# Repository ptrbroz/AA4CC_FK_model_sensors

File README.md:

# AA4CC_FK_model_sensors

FK_quadrature_decoder - DE0-Nano firmware for quadrature decoding and communication. Also includes folders from PC-side communication (python and matlab)

FK_fpga_shield - shield to be placed upon DE0-Nano

FK_encoder_shield - shield to be connected to each incremental encoder

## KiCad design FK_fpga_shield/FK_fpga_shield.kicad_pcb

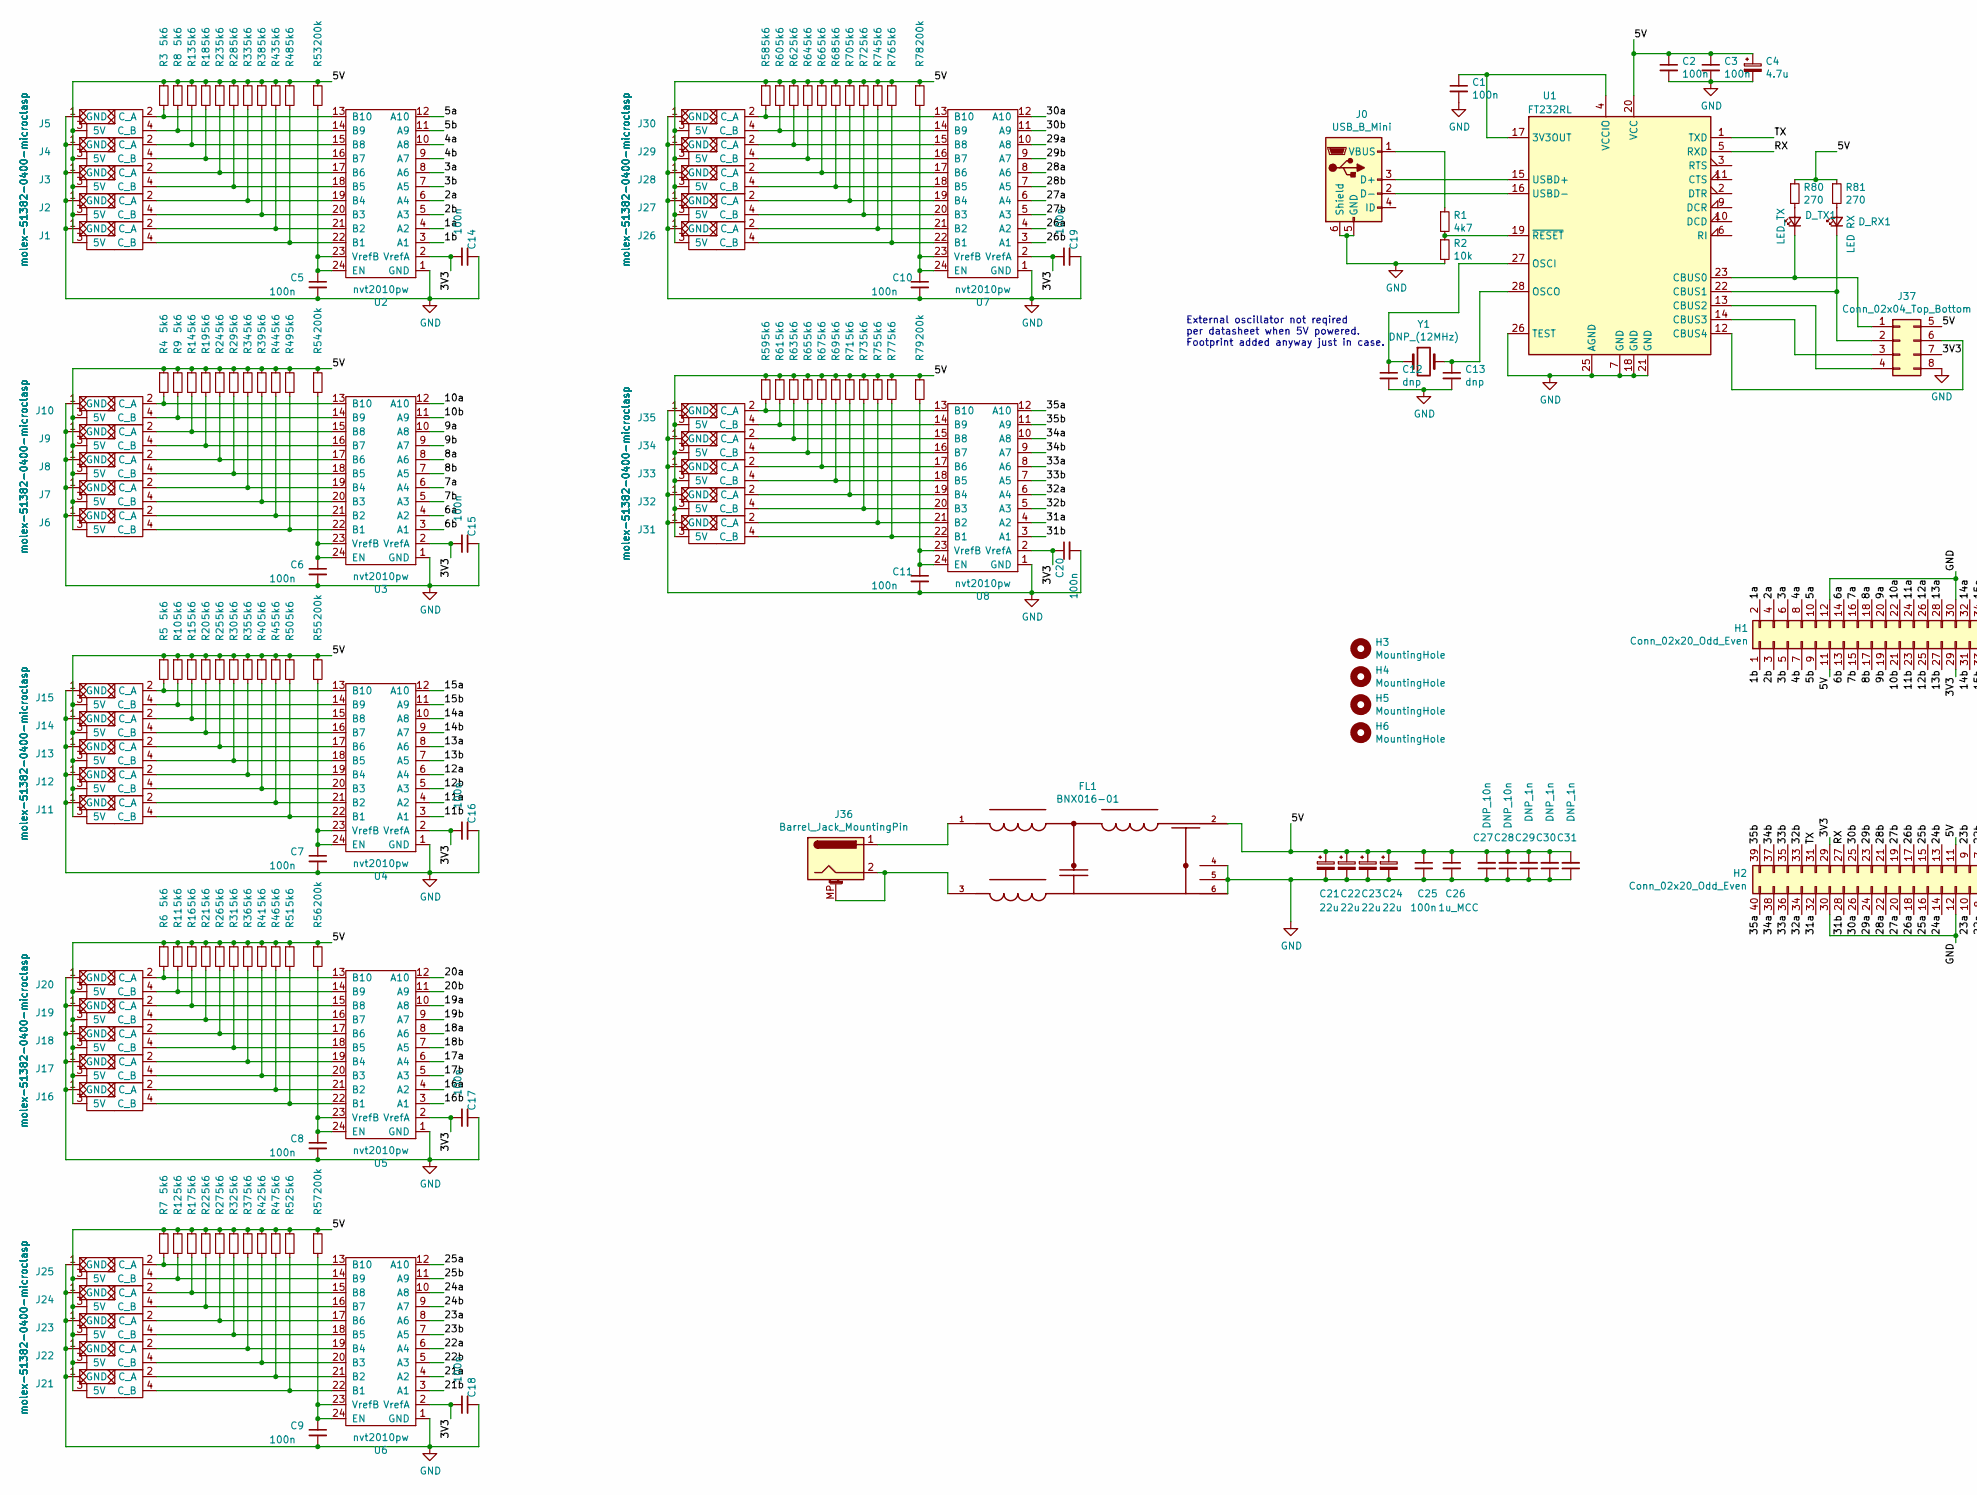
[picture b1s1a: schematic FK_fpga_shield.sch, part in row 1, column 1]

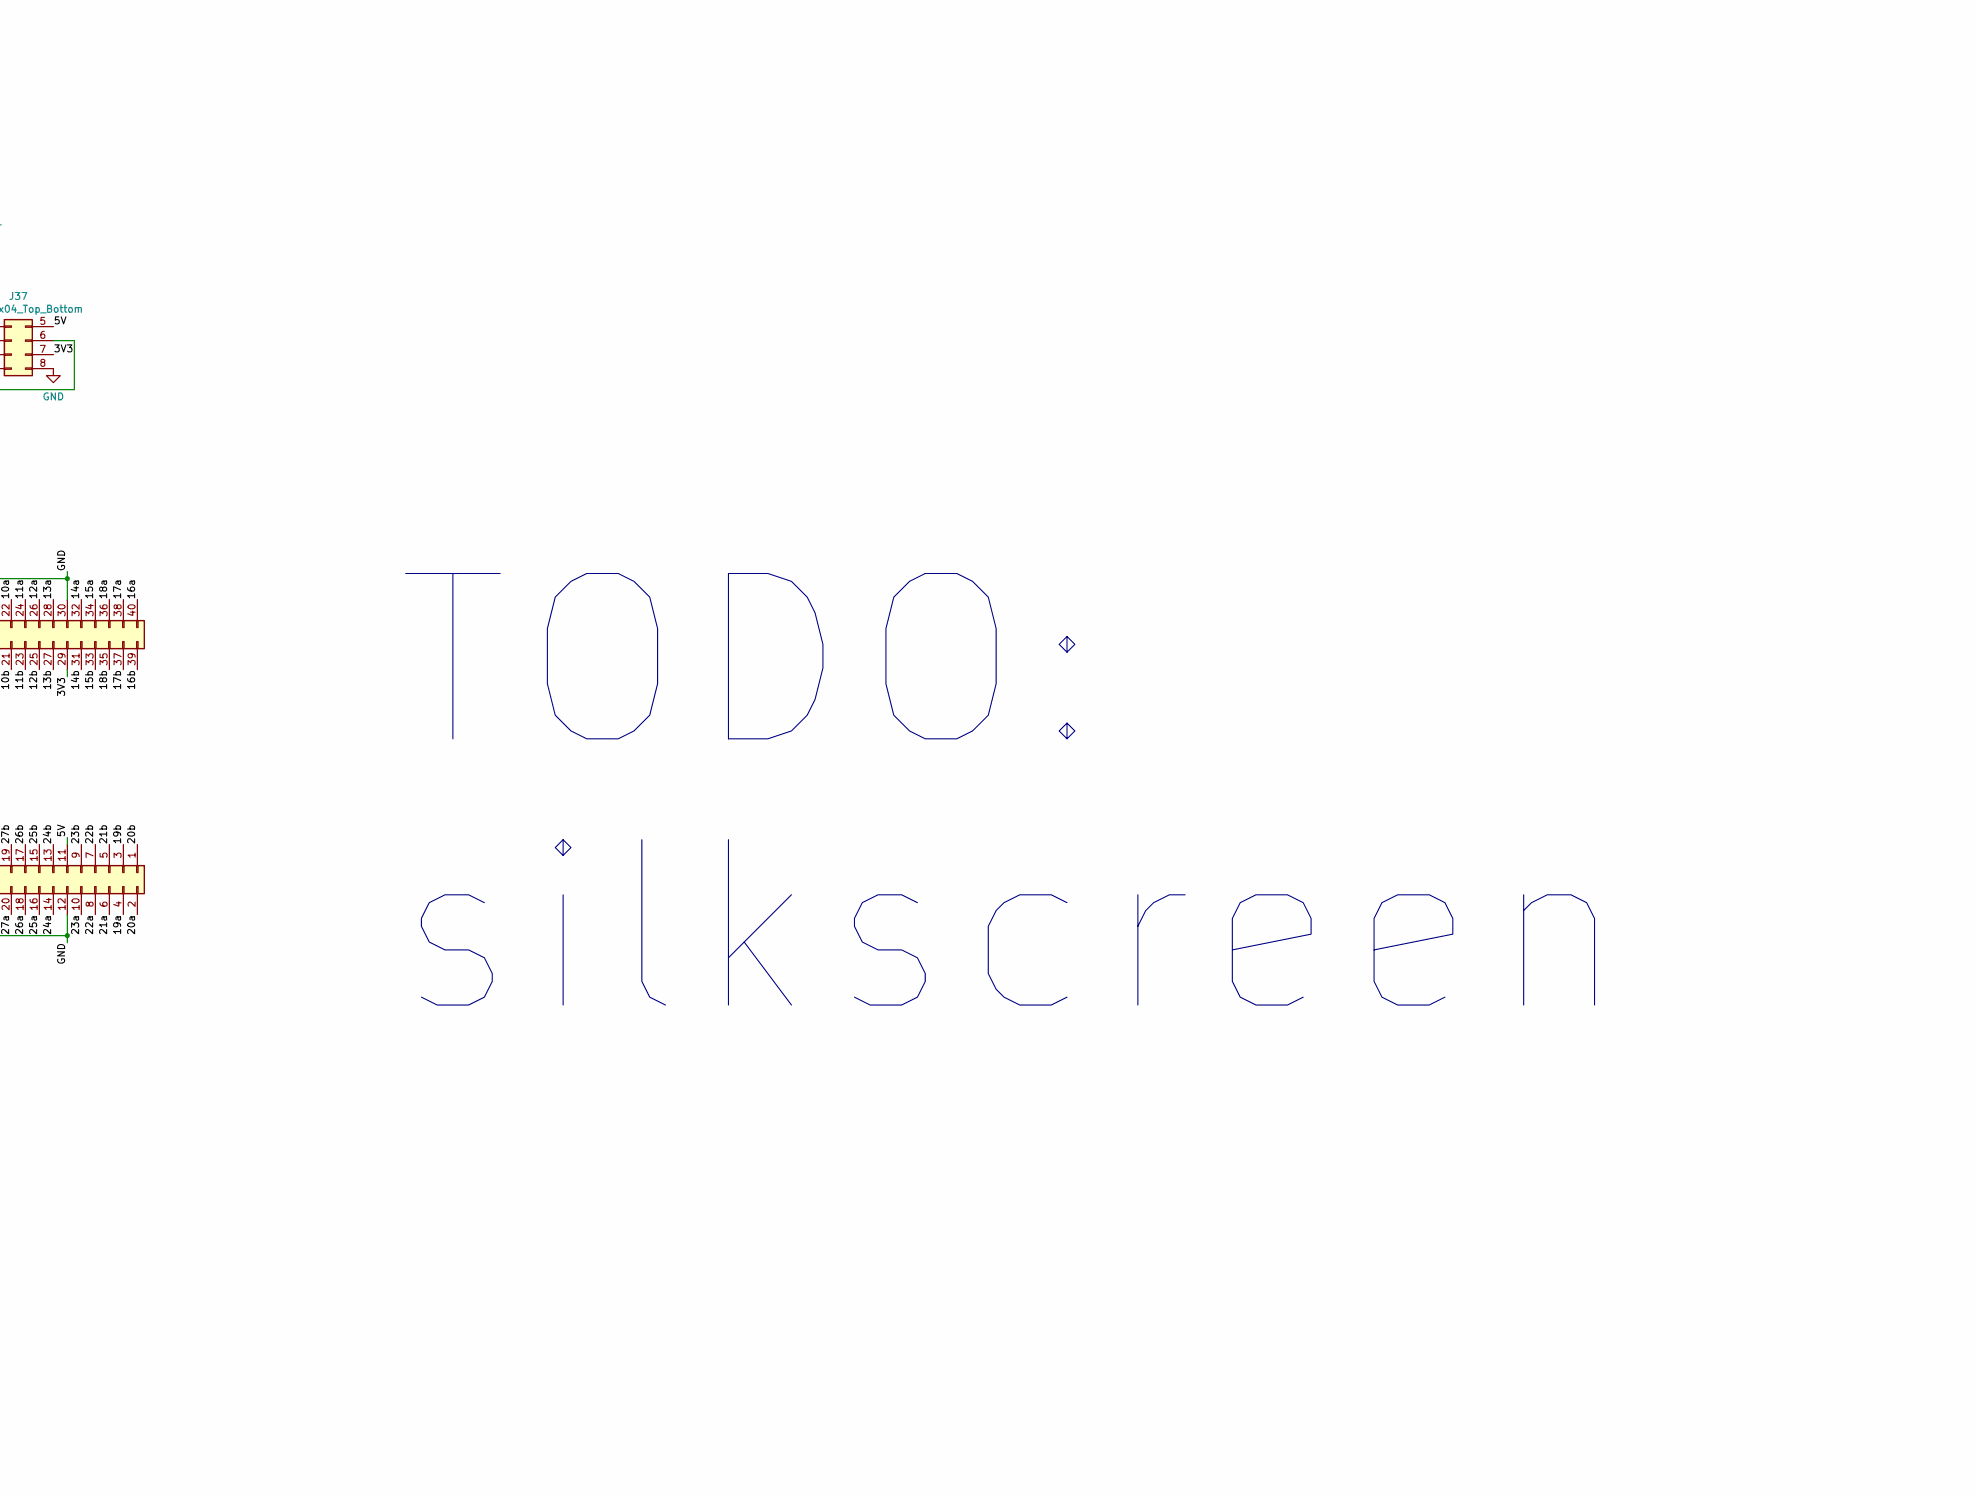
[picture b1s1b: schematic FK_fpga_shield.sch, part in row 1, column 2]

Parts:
C1, C2, C3, C5, C6, C7, C8, C9, C10, C11, C14, C15, C16, C17, C18, C19, C20, C25: 100n; C_0805_2012Metric_Pad1.15x1.40mm_HandSolder
C4: 4.7u; CP_Radial_D4.0mm_P1.50mm
C12, C13: dnp; C_0805_2012Metric_Pad1.15x1.40mm_HandSolder
C21, C22, C23, C24: 22u; CP_Radial_D6.3mm_P2.50mm
C26: 1u_MCC; C_0805_2012Metric_Pad1.15x1.40mm_HandSolder
C27, C28: DNP_10n; C_0805_2012Metric_Pad1.15x1.40mm_HandSolder
C29, C30, C31: DNP_1n; C_0805_2012Metric_Pad1.15x1.40mm_HandSolder
D_RX1: LED RX; LED_0805_2012Metric_Pad1.15x1.40mm_HandSolder
D_TX1: LED_TX; LED_0805_2012Metric_Pad1.15x1.40mm_HandSolder
FL1: BNX016-01; FIL_BNX016-01
H1, H2: Conn_02x20_Odd_Even; PinSocket_2x20_P2.54mm_Vertical
H3, H4, H5, H6: MountingHole; MountingHole_3mm
J0: USB_B_Mini; 54819-0519
J1, J2, J3, J4, J5, J6, J7, J8, J9, J10, J11, J12, J13, J14, J15, J16, J17, J18, J19, J20, J21, J22, J23, J24, J25, J26, J27, J28, J29, J30, J31, J32, J33, J34, J35: molex-51382-0400-microclasp; Molex_MicroClasp_55935-0410_1x04_P2.00mm_Horizontal
J36: Barrel_Jack_MountingPin; BarrelJack_CUI_PJ-063AH_Horizontal
J37: Conn_02x04_Top_Bottom; PinHeader_2x04_P2.54mm_Vertical
R1: 4k7; R_0805_2012Metric_Pad1.15x1.40mm_HandSolder
R2: 10k; R_0805_2012Metric_Pad1.15x1.40mm_HandSolder
R3, R4, R5, R6, R7, R8, R9, R10, R11, R12, R13, R14, R15, R16, R17, R18, R19, R20, R21, R22, R23, R24, R25, R26, R27, R28, R29, R30, R31, R32, R33, R34, R35, R36, R37, R38, R39, R40, R41, R42, R43, R44, R45, R46, R47, R48, R49, R50, R51, R52, R58, R59, R60, R61, R62, R63, R64, R65, R66, R67, R68, R69, R70, R71, R72, R73, R74, R75, R76, R77: 5k6; R_0805_2012Metric_Pad1.15x1.40mm_HandSolder
R53, R54, R55, R56, R57, R78, R79: 200k; R_0805_2012Metric_Pad1.15x1.40mm_HandSolder
R80, R81: 270; R_0805_2012Metric_Pad1.15x1.40mm_HandSolder
U1: FT232RL; SSOP-28_5.3x10.2mm_P0.65mm
U2, U3, U4, U5, U6, U7, U8: nvt2010pw; TSSOP-24_4.4x7.8mm_P0.65mm
Y1: DNP_(12MHz); Crystal_SMD_HC49-SD

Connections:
/1a: H1.2, U2.4 (A2)
/1b: H1.1, U2.3 (A1)
/2a: H1.4, U2.6 (A4)
/2b: H1.3, U2.5 (A3)
/3V3: C14.2, C15.2, C16.2, C17.2, C18.2, C19.2, C20.1, H1.29, H2.29, J37.7, U2.2 (VrefA), U3.2 (VrefA), U4.2 (VrefA), U5.2 (VrefA), U6.2 (VrefA), U7.2 (VrefA), U8.2 (VrefA)
/3a: H1.6, U2.8 (A6)
/3b: H1.5, U2.7 (A5)
/4a: H1.8, U2.10 (A8)
/4b: H1.7, U2.9 (A7)
/5V: C2.1, C3.1, C4.1, C21.1, C22.1, C23.1, C24.1, C25.1, C26.1, C27.2, C28.2, C29.2, C30.2, C31.2, FL1.2, H1.11, H2.11, J1.3 (5V), J2.3 (5V), J3.3 (5V), J4.3 (5V), J5.3 (5V), J6.3 (5V), J7.3 (5V), J8.3 (5V), J9.3 (5V), J10.3 (5V), J11.3 (5V), J12.3 (5V), J13.3 (5V), J14.3 (5V), J15.3 (5V), J16.3 (5V), J17.3 (5V), J18.3 (5V), J19.3 (5V), J20.3 (5V), J21.3 (5V), J22.3 (5V), J23.3 (5V), J24.3 (5V), J25.3 (5V), J26.3 (5V), J27.3 (5V), J28.3 (5V), J29.3 (5V), J30.3 (5V), J31.3 (5V), J32.3 (5V), J33.3 (5V), J34.3 (5V), J35.3 (5V), J37.5, R3.1, R4.1, R5.1, R6.1, R7.1, R8.1, R9.1, R10.1, R11.1, R12.1, R13.1, R14.1, R15.1, R16.1, R17.1, R18.1, R19.1, R20.1, R21.1, R22.1, R23.1, R24.1, R25.1, R26.1, R27.1, R28.1, R29.1, R30.1, R31.1, R32.1, R33.1, R34.1, R35.1, R36.1, R37.1, R38.1, R39.1, R40.1, R41.1, R42.1, R43.1, R44.1, R45.1, R46.1, R47.1, R48.1, R49.1, R50.1, R51.1, R52.1, R53.1, R54.1, R55.1, R56.1, R57.1, R58.1, R59.1, R60.1, R61.1, R62.1, R63.1, R64.1, R65.1, R66.1, R67.1, R68.1, R69.1, R70.1, R71.1, R72.1, R73.1, R74.1, R75.1, R76.1, R77.1, R78.1, R79.1, R80.1, R81.1, U1.20 (VCC)
/5a: H1.10, U2.12 (A10)
/5b: H1.9, U2.11 (A9)
/6a: H1.14, U3.4 (A2)
/6b: H1.13, U3.3 (A1)
/7a: H1.16, U3.6 (A4)
/7b: H1.15, U3.5 (A3)
/8a: H1.18, U3.8 (A6)
/8b: H1.17, U3.7 (A5)
/9a: H1.20, U3.10 (A8)
/9b: H1.19, U3.9 (A7)
/10a: H1.22, U3.12 (A10)
/10b: H1.21, U3.11 (A9)
/11a: H1.24, U4.4 (A2)
/11b: H1.23, U4.3 (A1)
/12a: H1.26, U4.6 (A4)
/12b: H1.25, U4.5 (A3)
/13a: H1.28, U4.8 (A6)
/13b: H1.27, U4.7 (A5)
/14a: H1.32, U4.10 (A8)
/14b: H1.31, U4.9 (A7)
/15a: H1.34, U4.12 (A10)
/15b: H1.33, U4.11 (A9)
/16a: H1.40, U5.4 (A2)
/16b: H1.39, U5.3 (A1)
/17a: H1.38, U5.6 (A4)
/17b: H1.37, U5.5 (A3)
/18a: H1.36, U5.8 (A6)
/18b: H1.35, U5.7 (A5)
/19a: H2.4, U5.10 (A8)
/19b: H2.3, U5.9 (A7)
/20a: H2.2, U5.12 (A10)
/20b: H2.1, U5.11 (A9)
/21a: H2.6, U6.4 (A2)
/21b: H2.5, U6.3 (A1)
/22a: H2.8, U6.6 (A4)
/22b: H2.7, U6.5 (A3)
/23a: H2.10, U6.8 (A6)
/23b: H2.9, U6.7 (A5)
/24a: H2.14, U6.10 (A8)
/24b: H2.13, U6.9 (A7)
/25a: H2.16, U6.12 (A10)
/25b: H2.15, U6.11 (A9)
/26a: H2.18, U7.4 (A2)
/26b: H2.17, U7.3 (A1)
/27a: H2.20, U7.6 (A4)
/27b: H2.19, U7.5 (A3)
/28a: H2.22, U7.8 (A6)
/28b: H2.21, U7.7 (A5)
/29a: H2.24, U7.10 (A8)
/29b: H2.23, U7.9 (A7)
/30a: H2.26, U7.12 (A10)
/30b: H2.25, U7.11 (A9)
/31a: H2.32, U8.4 (A2)
/31b: H2.28, U8.3 (A1)
/32a: H2.34, U8.6 (A4)
/32b: H2.33, U8.5 (A3)
/33a: H2.36, U8.8 (A6)
/33b: H2.35, U8.7 (A5)
/34a: H2.38, U8.10 (A8)
/34b: H2.37, U8.9 (A7)
/35a: H2.40, U8.12 (A10)
/35b: H2.39, U8.11 (A9)
/RX: H2.27, U1.5 (RXD)
/TX: H2.31, U1.1 (TXD)
GND: C1.2, C2.2, C3.2, C4.2, C5.2, C6.2, C7.2, C8.2, C9.2, C10.2, C11.2, C12.2, C13.2, C14.1, C15.1, C16.1, C17.1, C18.1, C19.1, C20.2, C21.2, C22.2, C23.2, C24.2, C25.2, C26.2, C27.1, C28.1, C29.1, C30.1, C31.1, FL1.4, FL1.5, FL1.6, H1.12, H1.30, H2.12, H2.30, J0.5 (GND), J0.6 (Shield), J1.1 (GND), J2.1 (GND), J3.1 (GND), J4.1 (GND), J5.1 (GND), J6.1 (GND), J7.1 (GND), J8.1 (GND), J9.1 (GND), J10.1 (GND), J11.1 (GND), J12.1 (GND), J13.1 (GND), J14.1 (GND), J15.1 (GND), J16.1 (GND), J17.1 (GND), J18.1 (GND), J19.1 (GND), J20.1 (GND), J21.1 (GND), J22.1 (GND), J23.1 (GND), J24.1 (GND), J25.1 (GND), J26.1 (GND), J27.1 (GND), J28.1 (GND), J29.1 (GND), J30.1 (GND), J31.1 (GND), J32.1 (GND), J33.1 (GND), J34.1 (GND), J35.1 (GND), J37.8, R2.2, U1.7 (GND), U1.18 (GND), U1.21 (GND), U1.25 (AGND), U1.26 (TEST), U2.1 (GND), U3.1 (GND), U4.1 (GND), U5.1 (GND), U6.1 (GND), U7.1 (GND), U8.1 (GND)
unnamed: C1.1, U1.4 (VCCIO), U1.17 (3V3OUT)
unnamed: C5.1, R53.2, U2.23 (VrefB), U2.24 (EN)
unnamed: C6.1, R54.2, U3.23 (VrefB), U3.24 (EN)
unnamed: C7.1, R55.2, U4.23 (VrefB), U4.24 (EN)
unnamed: C8.1, R56.2, U5.23 (VrefB), U5.24 (EN)
unnamed: C9.1, R57.2, U6.23 (VrefB), U6.24 (EN)
unnamed: C10.1, R78.2, U7.23 (VrefB), U7.24 (EN)
unnamed: C11.1, R79.2, U8.23 (VrefB), U8.24 (EN)
unnamed: C12.1, U1.27 (OSCI), Y1.1
unnamed: C13.1, U1.28 (OSCO), Y1.2
unnamed: D_RX1.1 (K), J37.2, U1.22 (CBUS1)
unnamed: D_RX1.2 (A), R81.2
unnamed: D_TX1.1 (K), J37.1, U1.23 (CBUS0)
unnamed: D_TX1.2 (A), R80.2
unnamed: FL1.1, J36.1
unnamed: FL1.3, J36.2, J36.MP (MountPin)
unnamed: J0.1 (VBUS), R1.1
unnamed: J0.2 (D-), U1.16 (USBD-)
unnamed: J0.3 (D+), U1.15 (USBD+)
unnamed: J1.2 (C_A), R43.2, U2.21 (B2)
unnamed: J1.4 (C_B), R48.2, U2.22 (B1)
unnamed: J2.2 (C_A), R33.2, U2.19 (B4)
unnamed: J2.4 (C_B), R38.2, U2.20 (B3)
unnamed: J3.2 (C_A), R23.2, U2.17 (B6)
unnamed: J3.4 (C_B), R28.2, U2.18 (B5)
unnamed: J4.2 (C_A), R13.2, U2.15 (B8)
unnamed: J4.4 (C_B), R18.2, U2.16 (B7)
unnamed: J5.2 (C_A), R3.2, U2.13 (B10)
unnamed: J5.4 (C_B), R8.2, U2.14 (B9)
unnamed: J6.2 (C_A), R44.2, U3.21 (B2)
unnamed: J6.4 (C_B), R49.2, U3.22 (B1)
unnamed: J7.2 (C_A), R34.2, U3.19 (B4)
unnamed: J7.4 (C_B), R39.2, U3.20 (B3)
unnamed: J8.2 (C_A), R24.2, U3.17 (B6)
unnamed: J8.4 (C_B), R29.2, U3.18 (B5)
unnamed: J9.2 (C_A), R14.2, U3.15 (B8)
unnamed: J9.4 (C_B), R19.2, U3.16 (B7)
unnamed: J10.2 (C_A), R4.2, U3.13 (B10)
unnamed: J10.4 (C_B), R9.2, U3.14 (B9)
unnamed: J11.2 (C_A), R45.2, U4.21 (B2)
unnamed: J11.4 (C_B), R50.2, U4.22 (B1)
unnamed: J12.2 (C_A), R35.2, U4.19 (B4)
unnamed: J12.4 (C_B), R40.2, U4.20 (B3)
unnamed: J13.2 (C_A), R25.2, U4.17 (B6)
unnamed: J13.4 (C_B), R30.2, U4.18 (B5)
unnamed: J14.2 (C_A), R15.2, U4.15 (B8)
unnamed: J14.4 (C_B), R20.2, U4.16 (B7)
unnamed: J15.2 (C_A), R5.2, U4.13 (B10)
unnamed: J15.4 (C_B), R10.2, U4.14 (B9)
unnamed: J16.2 (C_A), R46.2, U5.21 (B2)
unnamed: J16.4 (C_B), R51.2, U5.22 (B1)
unnamed: J17.2 (C_A), R36.2, U5.19 (B4)
unnamed: J17.4 (C_B), R41.2, U5.20 (B3)
unnamed: J18.2 (C_A), R26.2, U5.17 (B6)
unnamed: J18.4 (C_B), R31.2, U5.18 (B5)
unnamed: J19.2 (C_A), R16.2, U5.15 (B8)
unnamed: J19.4 (C_B), R21.2, U5.16 (B7)
unnamed: J20.2 (C_A), R6.2, U5.13 (B10)
unnamed: J20.4 (C_B), R11.2, U5.14 (B9)
unnamed: J21.2 (C_A), R47.2, U6.21 (B2)
unnamed: J21.4 (C_B), R52.2, U6.22 (B1)
unnamed: J22.2 (C_A), R37.2, U6.19 (B4)
unnamed: J22.4 (C_B), R42.2, U6.20 (B3)
unnamed: J23.2 (C_A), R27.2, U6.17 (B6)
unnamed: J23.4 (C_B), R32.2, U6.18 (B5)
unnamed: J24.2 (C_A), R17.2, U6.15 (B8)
unnamed: J24.4 (C_B), R22.2, U6.16 (B7)
unnamed: J25.2 (C_A), R7.2, U6.13 (B10)
unnamed: J25.4 (C_B), R12.2, U6.14 (B9)
unnamed: J26.2 (C_A), R74.2, U7.21 (B2)
unnamed: J26.4 (C_B), R76.2, U7.22 (B1)
unnamed: J27.2 (C_A), R70.2, U7.19 (B4)
unnamed: J27.4 (C_B), R72.2, U7.20 (B3)
unnamed: J28.2 (C_A), R66.2, U7.17 (B6)
unnamed: J28.4 (C_B), R68.2, U7.18 (B5)
unnamed: J29.2 (C_A), R62.2, U7.15 (B8)
unnamed: J29.4 (C_B), R64.2, U7.16 (B7)
unnamed: J30.2 (C_A), R58.2, U7.13 (B10)
unnamed: J30.4 (C_B), R60.2, U7.14 (B9)
unnamed: J31.2 (C_A), R75.2, U8.21 (B2)
unnamed: J31.4 (C_B), R77.2, U8.22 (B1)
unnamed: J32.2 (C_A), R71.2, U8.19 (B4)
unnamed: J32.4 (C_B), R73.2, U8.20 (B3)
unnamed: J33.2 (C_A), R67.2, U8.17 (B6)
unnamed: J33.4 (C_B), R69.2, U8.18 (B5)
unnamed: J34.2 (C_A), R63.2, U8.15 (B8)
unnamed: J34.4 (C_B), R65.2, U8.16 (B7)
unnamed: J35.2 (C_A), R59.2, U8.13 (B10)
unnamed: J35.4 (C_B), R61.2, U8.14 (B9)
unnamed: J37.3, U1.14 (CBUS3)
unnamed: J37.4, U1.13 (CBUS2)
unnamed: J37.6, U1.12 (CBUS4)
unnamed: R1.2, R2.1, U1.19 (~RESET~)

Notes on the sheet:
External oscillator not reqired per datasheet when 5V powered. Footprint added anyway just in case.
TODO: silkscreen

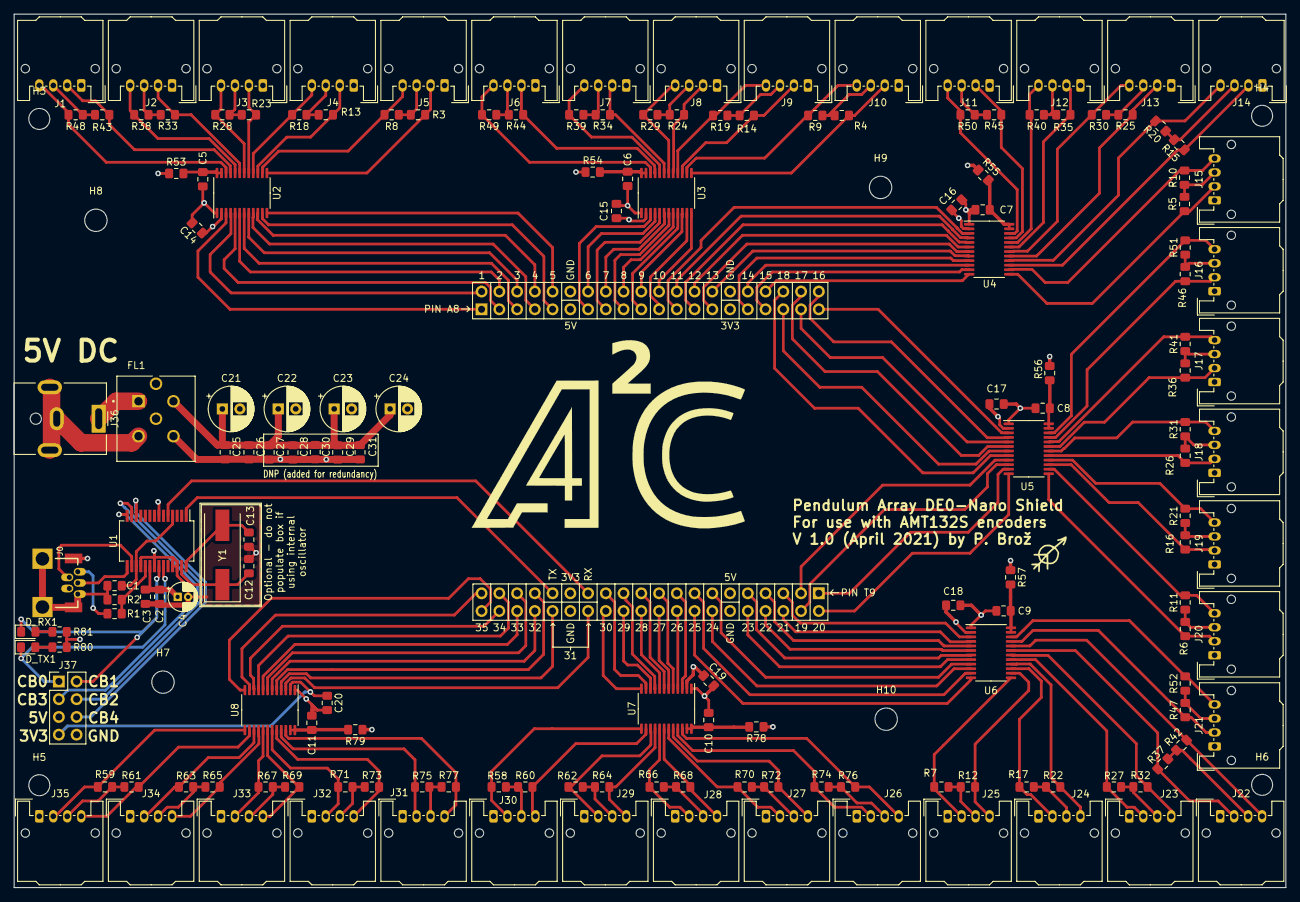
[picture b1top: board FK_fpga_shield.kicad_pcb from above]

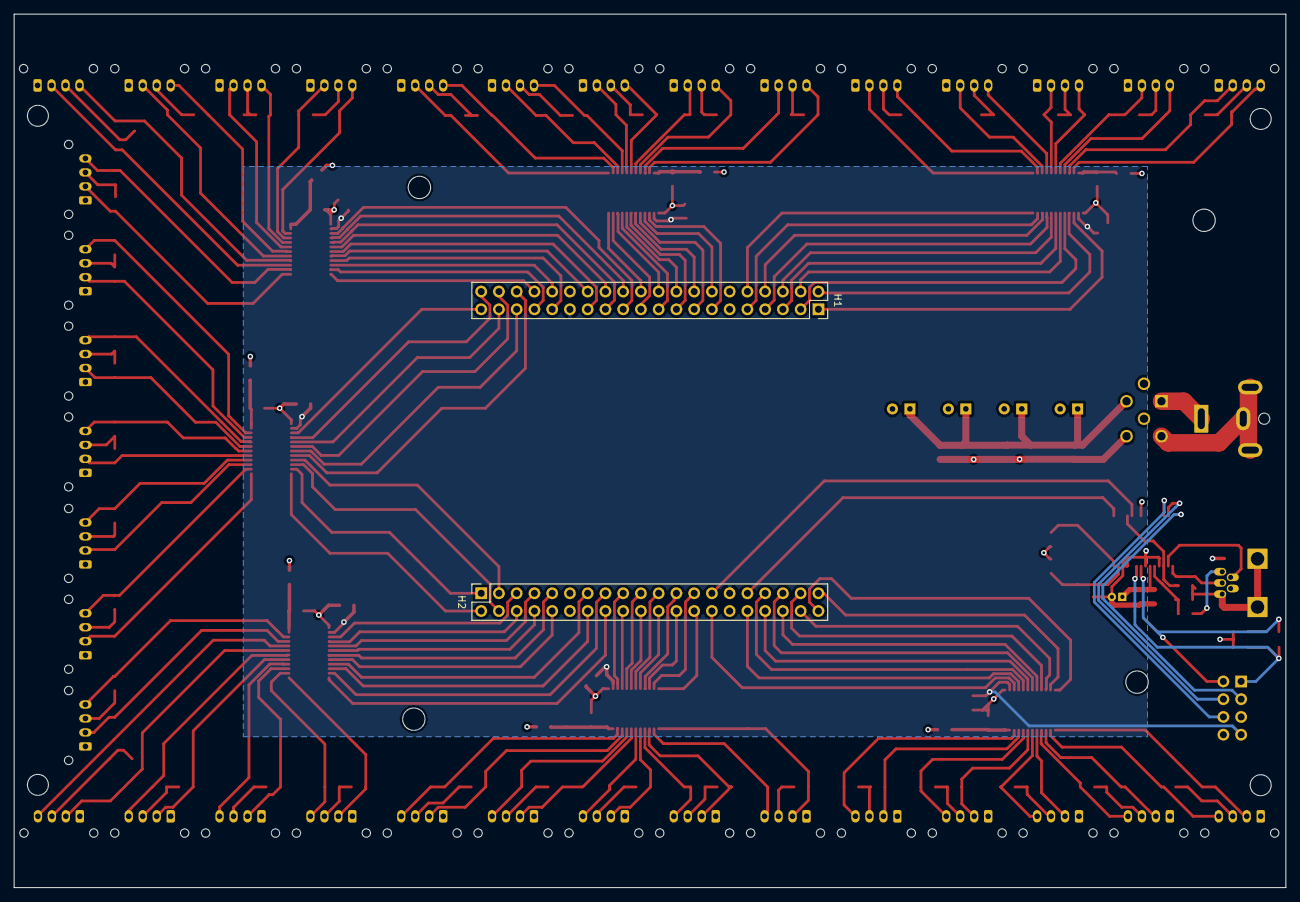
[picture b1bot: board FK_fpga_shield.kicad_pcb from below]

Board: 4 copper layers, 182.0 x 125.0 mm, 172 parts (2 on the bottom side), 168 nets.

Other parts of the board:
H7, H8, H9, H10: MountingHole; MountingHole_3.2mm_M3

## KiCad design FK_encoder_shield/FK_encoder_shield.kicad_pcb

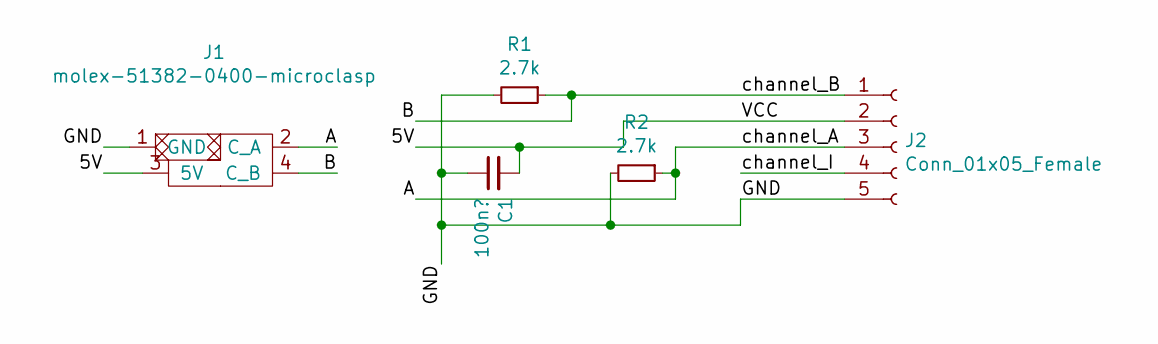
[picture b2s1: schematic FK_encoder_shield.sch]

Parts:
C1: 100n?; C_0805_2012Metric_Pad1.15x1.40mm_HandSolder
J1: molex-51382-0400-microclasp; Molex_MicroClasp_55935-0410_1x04_P2.00mm_Horizontal_3DMODEL
J2: Conn_01x05_Female; PinSocket_1x05_P2.54mm_Horizontal
R1, R2: 2.7k; R_0805_2012Metric_Pad1.15x1.40mm_HandSolder

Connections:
/5V: C1.2, J1.3 (5V), J2.2
/A: J1.2 (C_A), J2.3, R2.1
/B: J1.4 (C_B), J2.1, R1.1
/GND: C1.1, J1.1 (GND), J2.5, R1.2, R2.2
/channel_I: J2.4

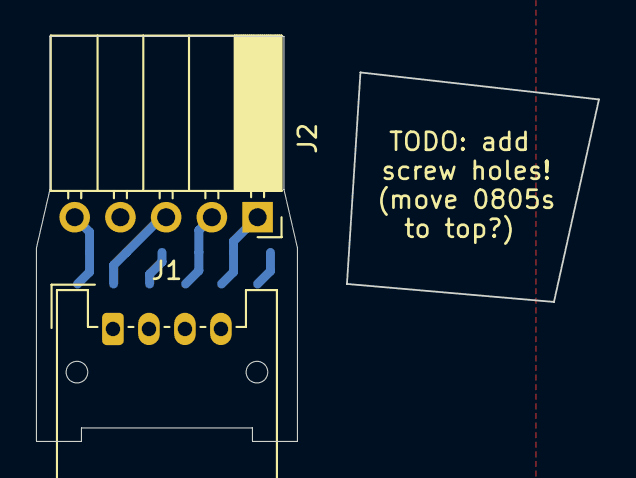
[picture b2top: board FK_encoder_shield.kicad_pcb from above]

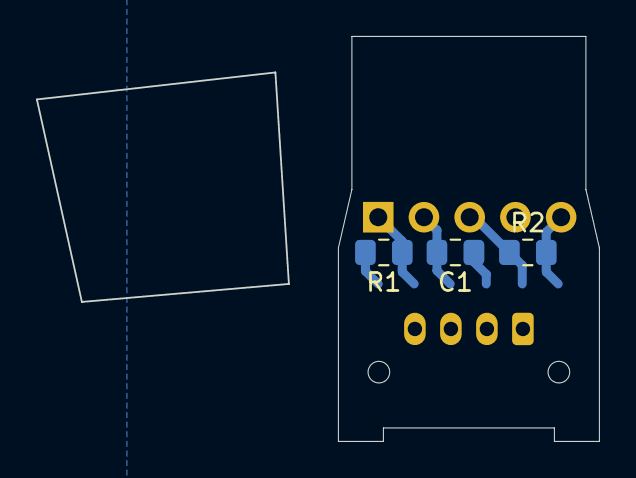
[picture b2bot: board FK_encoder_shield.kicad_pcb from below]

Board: 2 copper layers, 31.2 x 22.5 mm, 5 parts (3 on the bottom side), 4 nets.

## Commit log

2021-02-26 add quartus project
2021-02-27 pre conn symbol rework
2021-02-27 pre symbol update
2021-02-27 replace conn symbol on encoder shield
2021-02-27 change connector sym/footprint on fpgashield
2021-03-01 change connector to microclasp 4 wire
2021-03-01 add bom prep
2021-03-01 single level shifter schema
2021-03-01 WIP fpga shield layout
2021-03-01 wip lazyour (mapped to header)
2021-03-03 wip route before U4,U6 move
2021-03-03 levelshifter to fpga signals routed
2021-03-03 fix u6
2021-03-03 wip routing (usb done (?))
2021-03-04 decouple 3V3 references just in case
2021-03-05 redo 3v3 routing
2021-03-06 switch to 3V3 bottom layer plane, begin silkscreen
2021-03-06 silkscreen: main header
2021-03-06 silkscreen cosmetic fixes
2021-03-06 various silkscreen cometics
2021-03-08 choosen choke
2021-03-08 2x4 breakout header for uart convertor, choke laid out
2021-03-29 replace common mode choke with filter
2021-04-05 restore schematic from last version
2021-04-07 various minor
2021-04-08 mounting holes, silkscreen
2021-04-08 silkscrn fix
2021-04-09 gerbers etc
2021-04-09 remove unused encoder shield folder
2021-04-09 move gerber zip
2021-05-18 generate gerbers
2021-05-21 uart manager, watcher
2021-05-24 wip fail on integer signal
2021-05-24 Determine how bad naive implementation of watcher is (result: VERY.)
2021-05-26 rewrite watcher
2021-05-26 wip hw test
2021-05-26 pin assignments, update gitignore
    rtl viewer still looking kinda wonky, maybe try to toss buffer type and return to output in watcher?
2021-05-26 remove (hopefully) ignored files
2021-05-27 comms byte skipping fix
2021-05-27 pre test
2021-05-27 comms tested with 1 encoder
2021-05-31 comms receiving
2021-06-01 wip boss.vhd
2021-06-01 wip connect boss and rest
2021-06-01 boss bugfixes
2021-06-02 fix boss echo
2021-06-02 wip fixing printing-related bug
2021-06-02 fix resolution echo
2021-06-02 expand data signals to work with 35 encoders at 13 bits
2021-06-02 wip set delay (boss doesn|t echo last byte)
2021-06-07 monday start
2021-06-07 code prettifications
2021-06-07 fix ordering issue in encoder enable vector
2021-06-07 rename generated wires
2021-06-07 python prettify
2021-06-08 quartus project cleanup
2021-06-08 remove unused constants, rename programming files
2021-06-09 add wip manual
2021-06-09 manual update
2021-06-11 add section on cabling to manual
2021-06-23 turning off
2022-01-26 add revolution tracking to quad decoder
2022-01-26 watcher logic for revolution printing
2022-01-26 syntax fixes in watcher
2022-01-26 fix wire len
2022-01-26 add logic for setting resolution in boss
2022-01-26 connect revresolution logic
2022-01-27 update python comm demo
2022-01-27 wip manual update to reflect revolution tracking feature
2022-06-05 update manual comms section (adds pictures for revolution messages)
2022-06-07 track jpg files
2022-07-04 wip simulink block
2022-07-07 add fpga config, reading of all positions and revolutions to simulink block
2022-07-07 add comments where serial will need to be replaced with codegen friendly stuff
2022-07-14 wip simulink schema
2022-07-14 remove old folder
2022-07-14 wip - this version simulates via code generation and seems to receive data from device
2022-07-14 add setup file
2022-07-15 full message reading with header
2022-07-15 wip configuration
2022-07-15 Appears to work correctly. Problem with occasional lag (just simulink running slow, hopefully?)
2022-07-15 cleanup
2022-07-15 more cleanup
2022-07-15 set baudrate via fkReaderSetup. Remove port name from setup since it can't be used by instrument control toolbox
2022-08-16 Add feature: After sending config reply message, wait twice normal messaging period before starting to send data messages.
2022-08-16 Add feature: setting zero communication period now switches device to single message mode. In this mode, data messages are not sent periodically. Instead, they are sent only when requested by user (w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
2022-08-24 manual update (add pcb bug fix description, add firmware structure overview)
2022-09-05 added python scrip for on-demand communication, tested with encoders.
2022-10-03 pcb update for new kicad
2022-10-03 add uart to bottom header
